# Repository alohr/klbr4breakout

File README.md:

Lumberg KLBR4 breakout board
============================

None of the 3.5mm audio jacks I know of fit on a standard breadboard. Here is a breakout board for the
"Lumberg KLBR4" audio jack to fix this.

## Board layout

## Examples

Where to get
============

## Audio jack

[Reichelt Elektronik (Germany)](http://www.reichelt.de/LUM-KLBR-4/3/index.html?&ACTION=3&LA=446&ARTICLE=116186&artnr=LUM+KLBR+4&SEARCH=klbr4)

## PCB

[OSH Park - klbr4 breakout](https://oshpark.com/shared_projects/lQV1U9tV)

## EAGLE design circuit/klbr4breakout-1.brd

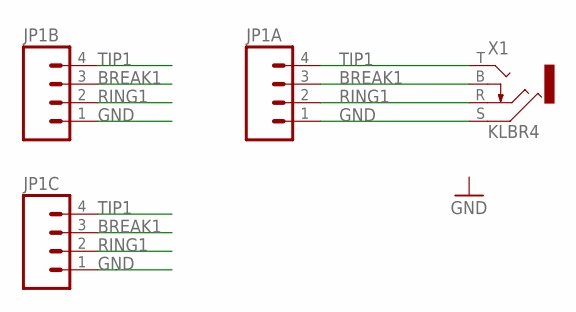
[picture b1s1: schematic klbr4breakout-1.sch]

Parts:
JP1A, JP1B, JP1C: M04PTH; 1X04
X1: KLBR4

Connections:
BREAK1: JP1A.3, JP1B.3, JP1C.3, X1.B
GND: JP1A.1, JP1B.1, JP1C.1, X1.S
RING1: JP1A.2, JP1B.2, JP1C.2, X1.R
TIP1: JP1A.4, JP1B.4, JP1C.4, X1.T

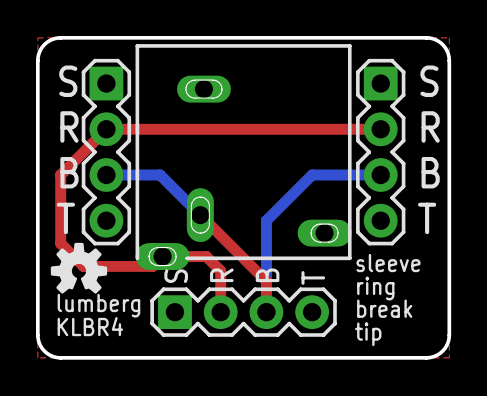
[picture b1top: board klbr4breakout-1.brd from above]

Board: 2 copper layers, 22.9 x 17.8 mm, 5 parts (0 on the bottom side), 4 nets.

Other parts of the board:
U$1: OSHW-LOGO-S

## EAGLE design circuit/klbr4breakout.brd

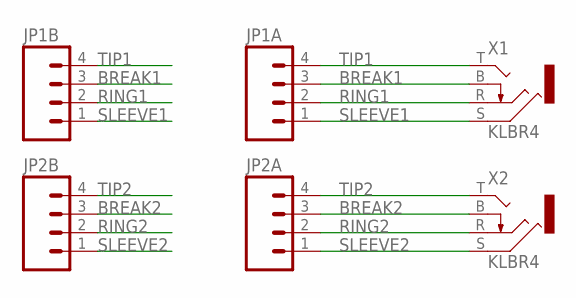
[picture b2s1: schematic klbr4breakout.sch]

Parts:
JP1A, JP1B, JP2A, JP2B: M04PTH; 1X04
X1, X2: KLBR4

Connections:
BREAK1: JP1A.3, JP1B.3, X1.B
BREAK2: JP2A.3, JP2B.3, X2.B
RING1: JP1A.2, JP1B.2, X1.R
RING2: JP2A.2, JP2B.2, X2.R
SLEEVE1: JP1A.1, JP1B.1, X1.S
SLEEVE2: JP2A.1, JP2B.1, X2.S
TIP1: JP1A.4, JP1B.4, X1.T
TIP2: JP2A.4, JP2B.4, X2.T

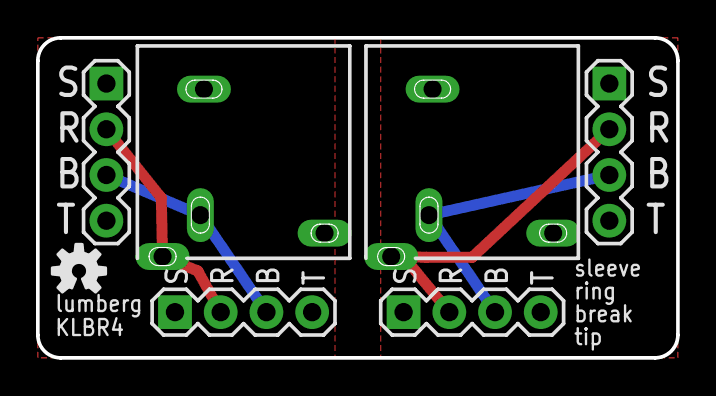
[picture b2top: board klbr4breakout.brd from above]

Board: 2 copper layers, 35.6 x 17.8 mm, 7 parts (0 on the bottom side), 8 nets.

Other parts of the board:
U$1: OSHW-LOGO-S

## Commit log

2015-08-30 moved eagle files to circuit
2015-08-30 added images
2015-08-30 fixed filenames
2015-08-30 fixed links
2024-12-06 add single connector board

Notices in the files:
parts and their libraries:
SparkFun-Connectors: Licensing: CC v3.0 Share-Alike You are welcome to use this library for commercial purposes.
